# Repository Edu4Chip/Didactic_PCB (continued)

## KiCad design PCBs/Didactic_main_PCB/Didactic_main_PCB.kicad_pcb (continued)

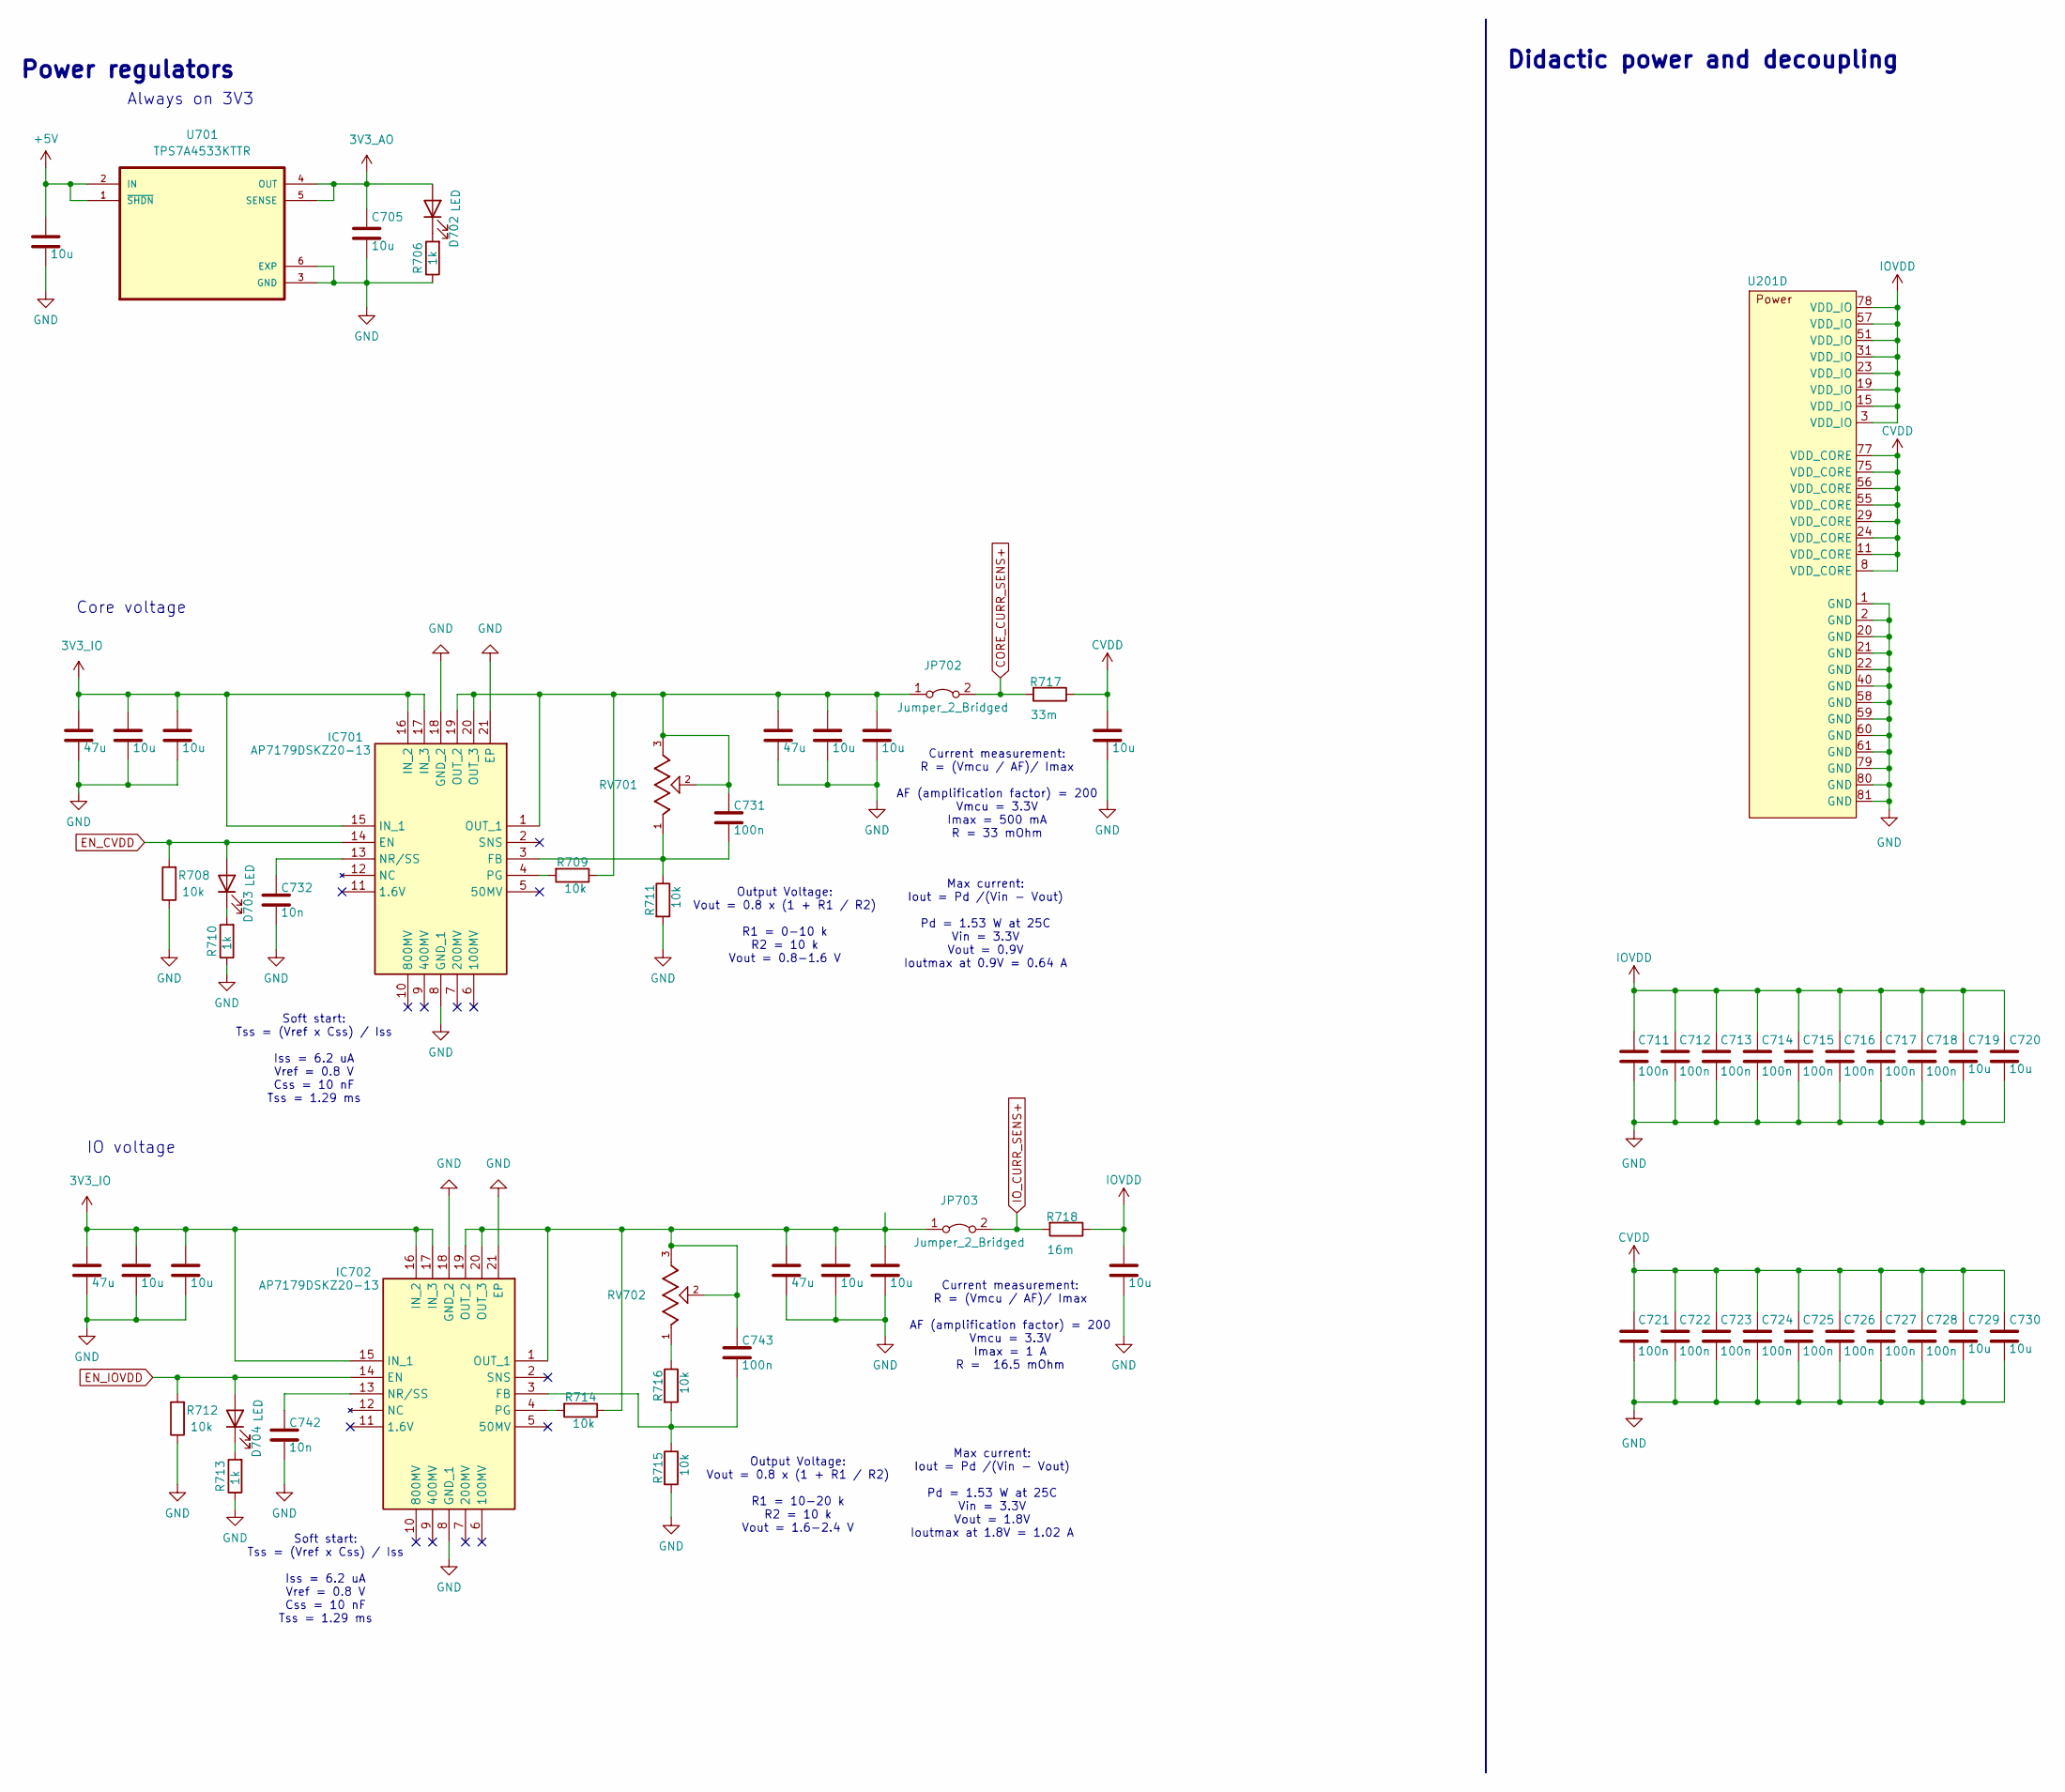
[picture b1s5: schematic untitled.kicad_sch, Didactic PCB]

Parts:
C703, C705, C719, C720, C729, C730, C734, C735, C737, C738, C740, C741, C745, C746, C747, C748: 10u; C_0805_2012Metric; MANUFACTURER_PART_NUMBER GPC0805106-25
C711, C712, C713, C714, C715, C716, C717, C718, C721, C722, C723, C724, C725, C726, C727, C728, C731, C743: 100n; C_0603_1608Metric; MANUFACTURER_PART_NUMBER GPC0603104
C732, C742: 10n; C_0603_1608Metric; MANUFACTURER_PART_NUMBER GPC0603103
C733, C736, C739, C744: 47u; C_0805_2012Metric; MANUFACTURER_PART_NUMBER GPC0805476-6.3
D702, D703, D704: LED; LED_0603_1608Metric; MANUFACTURER_PART_NUMBER APHD1608LSURCK
IC701, IC702: AP7179DSKZ20-13; QFN50P350X350X80-21N-D; Manufacturer_Part_Number AP7179DSKZ20-13
JP702, JP703: Jumper_2_Bridged; PinHeader_1x02_P2.54mm_Vertical; MANUFACTURER_PART_NUMBER 61300211121
R706, R710, R713: 1k; R_0603_1608Metric; MANUFACTURER_PART_NUMBER GPR06031K
R708, R709, R711, R712, R714, R715, R716: 10k; R_0603_1608Metric; MANUFACTURER_PART_NUMBER GPR060310K
R717: 33m; R_1206_3216Metric; MANUFACTURER_PART_NUMBER ERJ-8CWFR033V
R718: 16m; R_1206_3216Metric; MANUFACTURER_PART_NUMBER ERJ-8CWFR016V
RV701, RV702: PV36W103C01B00; TRIM_PV36W103C01B00; PARTREV N/A
U201: Didactic_QFN-80_EP_12x12_Pitch0.5mm
U701: TPS7A4533KTTR; VREG_TPS79625KTTR; MANUFACTURER_PART_NUMBER TPS7A4533KTTR

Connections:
3V3_AO: C705.2, D702.2 (A), U701.4 (OUT), U701.5 (SENSE); also elsewhere on the board
3V3_IO: C736.2, C737.2, C738.2, C739.2, C740.2, C741.2, IC701.15 (IN_1), IC701.16 (IN_2), IC701.17 (IN_3), IC702.15 (IN_1), IC702.16 (IN_2), IC702.17 (IN_3); also elsewhere on the board
+5V: C703.2, U701.1 (~SHDN), U701.2 (IN); also elsewhere on the board
CORE_CURR_SENS+: JP702.2 (B), R717.2; also elsewhere on the board
CVDD: C721.2, C722.2, C723.2, C724.2, C725.2, C726.2, C727.2, C728.2, C729.2, C730.2, C747.2, R717.1, U201.8 (VDD_CORE), U201.11 (VDD_CORE), U201.24 (VDD_CORE), U201.29 (VDD_CORE), U201.55 (VDD_CORE), U201.56 (VDD_CORE), U201.75 (VDD_CORE), U201.77 (VDD_CORE); also elsewhere on the board
EN_CVDD: D703.2 (A), IC701.14 (EN), R708.2; also elsewhere on the board
EN_IOVDD: D704.2 (A), IC702.14 (EN), R712.2; also elsewhere on the board
GND: C703.1, C705.1, C711.1, C712.1, C713.1, C714.1, C715.1, C716.1, C717.1, C718.1, C719.1, C720.1, C721.1, C722.1, C723.1, C724.1, C725.1, C726.1, C727.1, C728.1, C729.1, C730.1, C732.2, C733.1, C734.1, C735.1, C736.1, C737.1, C738.1, C739.1, C740.1, C741.1, C742.2, C744.1, C745.1, C746.1, C747.1, C748.1, IC701.8 (GND_1), IC701.18 (GND_2), IC701.21 (EP), IC702.8 (GND_1), IC702.18 (GND_2), IC702.21 (EP), R706.1, R708.1, R710.1, R711.2, R712.1, R713.1, R715.2, U201.1 (GND), U201.2 (GND), U201.20 (GND), U201.21 (GND), U201.22 (GND), U201.40 (GND), U201.58 (GND), U201.59 (GND), U201.60 (GND), U201.61 (GND), U201.79 (GND), U201.80 (GND), U201.81 (GND), U701.3 (GND), U701.6 (EXP); also elsewhere on the board
IOVDD: C711.2, C712.2, C713.2, C714.2, C715.2, C716.2, C717.2, C718.2, C719.2, C720.2, C748.2, R718.1, U201.3 (VDD_IO), U201.15 (VDD_IO), U201.19 (VDD_IO), U201.23 (VDD_IO), U201.31 (VDD_IO), U201.51 (VDD_IO), U201.57 (VDD_IO), U201.78 (VDD_IO); also elsewhere on the board
IO_CURR_SENS+: JP703.2 (B), R718.2; also elsewhere on the board
unnamed: D702.1 (K), R706.2
unnamed: D703.1 (K), R710.2
unnamed: D704.1 (K), R713.2
unnamed: C731.2, IC701.3 (FB), R711.1, RV701.1
unnamed: C732.1, IC701.13 (NR/SS)
unnamed: C731.1, C733.2, C734.2, C735.2, IC701.1 (OUT_1), IC701.19 (OUT_2), IC701.20 (OUT_3), JP702.1 (A), R709.1, RV701.2, RV701.3
unnamed: IC701.4 (PG), R709.2
unnamed: C743.2, IC702.3 (FB), R715.1, R716.2
unnamed: C742.1, IC702.13 (NR/SS)
unnamed: C743.1, C744.2, C745.2, C746.2, IC702.1 (OUT_1), IC702.19 (OUT_2), IC702.20 (OUT_3), JP703.1 (A), R714.1, RV702.2, RV702.3
unnamed: IC702.4 (PG), R714.2
unnamed: R716.1, RV702.1

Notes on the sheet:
Current measurement: R = (Vmcu / AF)/ Imax AF (amplification factor) = 200 Vmcu = 3.3V Imax = 1 A R = 16.5 mOhm
IO voltage
Soft start: Tss = (Vref x Css) / Iss Iss = 6.2 uA Vref = 0.8 V Css = 10 nF Tss = 1.29 ms
Max current: Iout = Pd /(Vin - Vout) Pd = 1.53 W at 25C Vin = 3.3V Vout = 0.9V Ioutmax at 0.9V = 0.64 A
Output Voltage: Vout = 0.8 x (1 + R1 / R2) R1 = 10-20 k R2 = 10 k Vout = 1.6-2.4 V
Always on 3V3
Core voltage
Power regulators
Didactic power and decoupling
Max current: Iout = Pd /(Vin - Vout) Pd = 1.53 W at 25C Vin = 3.3V Vout = 1.8V Ioutmax at 1.8V = 1.02 A
Current measurement: R = (Vmcu / AF)/ Imax AF (amplification factor) = 200 Vmcu = 3.3V Imax = 500 mA R = 33 mOhm
Output Voltage: Vout = 0.8 x (1 + R1 / R2) R1 = 0-10 k R2 = 10 k Vout = 0.8-1.6 V

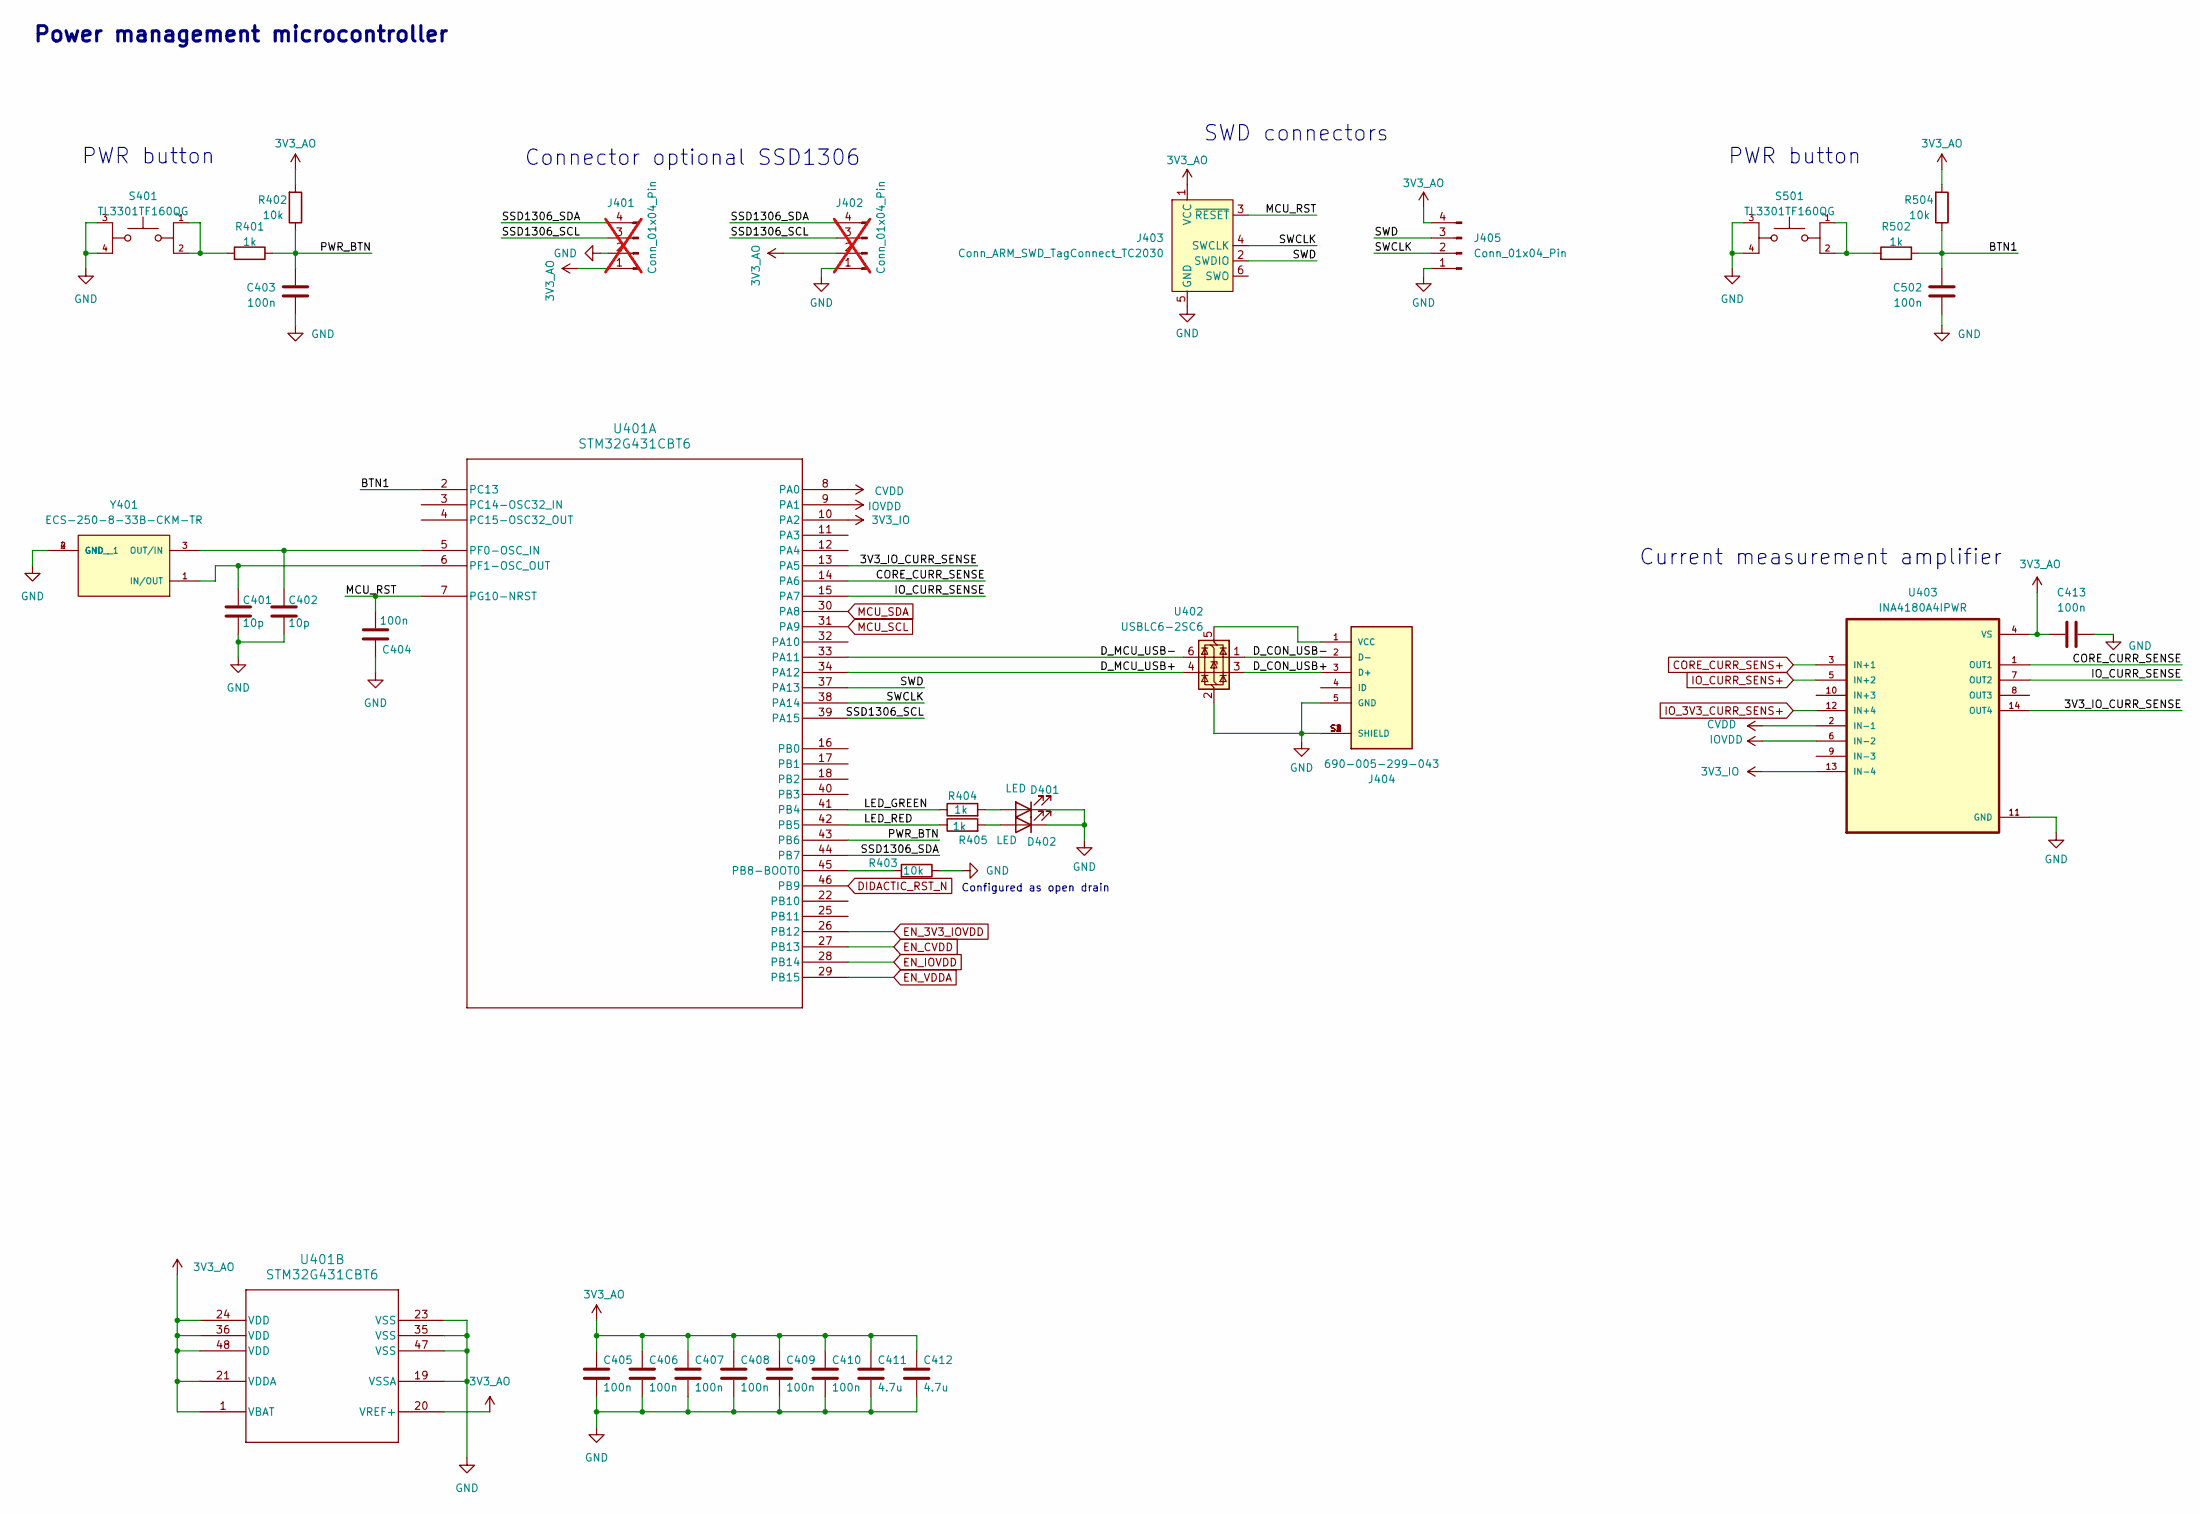
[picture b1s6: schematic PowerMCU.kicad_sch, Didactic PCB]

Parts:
C401, C402: 10p; C_0603_1608Metric; MANUFACTURER_PART_NUMBER GPC0603100
C403, C404, C405, C406, C407, C408, C409, C410, C413, C502: 100n; C_0603_1608Metric; MANUFACTURER_PART_NUMBER GPC0603104
C411, C412: 4.7u; C_0603_1608Metric; MANUFACTURER_PART_NUMBER GPC0603475-10
D401: LED; LED_0603_1608Metric; MANUFACTURER_PART_NUMBER APHD1608LCGCK
D402: LED; LED_0603_1608Metric; MANUFACTURER_PART_NUMBER APHD1608LSURCK
J401, J402: Conn_01x04_Pin; PinHeader_1x04_P2.54mm_Vertical; MANUFACTURER_PART_NUMBER 77311-424-04LF; not fitted
J403: Conn_ARM_SWD_TagConnect_TC2030; Tag-Connect_TC2030-IDC-FP_2x03_P1.27mm_Vertical
J404: 690-005-299-043; EDAC_690-005-299-043; PARTREV 11
J405: Conn_01x04_Pin; PinHeader_1x04_P2.54mm_Vertical; MANUFACTURER_PART_NUMBER 77311-424-04LF
R401, R404, R405, R502: 1k; R_0603_1608Metric; MANUFACTURER_PART_NUMBER GPR06031K
R402, R403, R504: 10k; R_0603_1608Metric; MANUFACTURER_PART_NUMBER GPR060310K
S401, S501: TL3301TF160QG; SW_TL3301TF160QG; PARTREV E
U401: STM32G431CBT6; LQFP48-7x7mm; MANUFACTURER_PART_NUMBER STM32G431CBT6
U402: USBLC6-2SC6; SOT-23-6; MANUFACTURER_PART_NUMBER USBLC6-2SC6
U403: INA4180A4IPWR; SOP65P640X120-14N; MANUFACTURER_PART_NUMBER INA4180A4IPWR
Y401: ECS-250-8-33B-CKM-TR; XTAL_ECS-250-8-33B-CKM-TR; MANUFACTURER_PART_NUMBER ECS-250-8-33B-CKM-TR

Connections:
3V3_AO: C405.2, C406.2, C407.2, C408.2, C409.2, C410.2, C411.2, C412.2, C413.1, J401.1, J402.2, J403.1 (VCC), J405.4, R402.2, R504.2, U401.1 (VBAT), U401.20 (VREF+), U401.21 (VDDA), U401.24 (VDD), U401.36 (VDD), U401.48 (VDD), U403.4 (VS); also elsewhere on the board
3V3_IO: U401.10 (PA2), U403.13 (IN-4); also elsewhere on the board
/PowerMCU/3V3_IO_CURR_SENSE: U401.13 (PA5), U403.14 (OUT4)
/PowerMCU/BTN1: C502.1, R502.1, R504.1, U401.2 (PC13)
/PowerMCU/CORE_CURR_SENSE: U401.14 (PA6), U403.1 (OUT1)
/PowerMCU/D_CON_USB+: J404.3 (D+), U402.3 (I/O2)
/PowerMCU/D_CON_USB-: J404.2 (D-), U402.1 (I/O1)
/PowerMCU/D_MCU_USB+: U401.34 (PA12), U402.4 (I/O2)
/PowerMCU/D_MCU_USB-: U401.33 (PA11), U402.6 (I/O1)
/PowerMCU/IO_CURR_SENSE: U401.15 (PA7), U403.7 (OUT2)
/PowerMCU/LED_GREEN: R404.1, U401.41 (PB4)
/PowerMCU/LED_RED: R405.1, U401.42 (PB5)
/PowerMCU/MCU_RST: C404.2, J403.3 (~RESET), U401.7 (PG10-NRST)
/PowerMCU/PWR_BTN: C403.1, R401.1, R402.1, U401.43 (PB6)
/PowerMCU/SSD1306_SCL: J401.3, J402.3, U401.39 (PA15)
/PowerMCU/SSD1306_SDA: J401.4, J402.4, U401.44 (PB7)
/PowerMCU/SWCLK: J403.4 (SWCLK), J405.2, U401.38 (PA14)
/PowerMCU/SWD: J403.2 (SWDIO), J405.3, U401.37 (PA13)
CORE_CURR_SENS+: U403.3 (IN+1); also elsewhere on the board
CVDD: U401.8 (PA0), U403.2 (IN-1); also elsewhere on the board
DIDACTIC_RST_N: U401.46 (PB9); also elsewhere on the board
EN_3V3_IOVDD: U401.26 (PB12); also elsewhere on the board
EN_CVDD: U401.27 (PB13); also elsewhere on the board
EN_IOVDD: U401.28 (PB14); also elsewhere on the board
EN_VDDA: U401.29 (PB15)
GND: C401.2, C402.2, C403.2, C404.1, C405.1, C406.1, C407.1, C408.1, C409.1, C410.1, C411.1, C412.1, C413.2, C502.2, D401.1 (K), D402.1 (K), J401.2, J402.1, J403.5 (GND), J404.5 (GND), J404.S1 (SHIELD), J404.S2 (SHIELD), J404.S3 (SHIELD), J404.S4 (SHIELD), J405.1, R403.1, S401.3, S401.4, S501.3, S501.4, U401.19 (VSSA), U401.23 (VSS), U401.35 (VSS), U401.47 (VSS), U402.2 (GND), U403.11 (GND), Y401.2 (GND), Y401.4 (GND__1); also elsewhere on the board
IOVDD: U401.9 (PA1), U403.6 (IN-2); also elsewhere on the board
IO_3V3_CURR_SENS+: U403.12 (IN+4); also elsewhere on the board
IO_CURR_SENS+: U403.5 (IN+2); also elsewhere on the board
MCU_SCL: U401.31 (PA9); also elsewhere on the board
MCU_SDA: U401.30 (PA8); also elsewhere on the board
unnamed: D401.2 (A), R404.2
unnamed: D402.2 (A), R405.2
unnamed: J404.1 (VCC), U402.5 (VBUS)
unnamed: R401.2, S401.1, S401.2
unnamed: R502.2, S501.1, S501.2
unnamed: R403.2, U401.45 (PB8-BOOT0)
unnamed: C402.1, U401.5 (PF0-OSC_IN), Y401.3 (OUT/IN)
unnamed: C401.1, U401.6 (PF1-OSC_OUT), Y401.1 (IN/OUT)

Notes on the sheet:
PWR button
Power management microcontroller
Connector optional SSD1306
Configured as open drain
SWD connectors
Current measurement amplifier

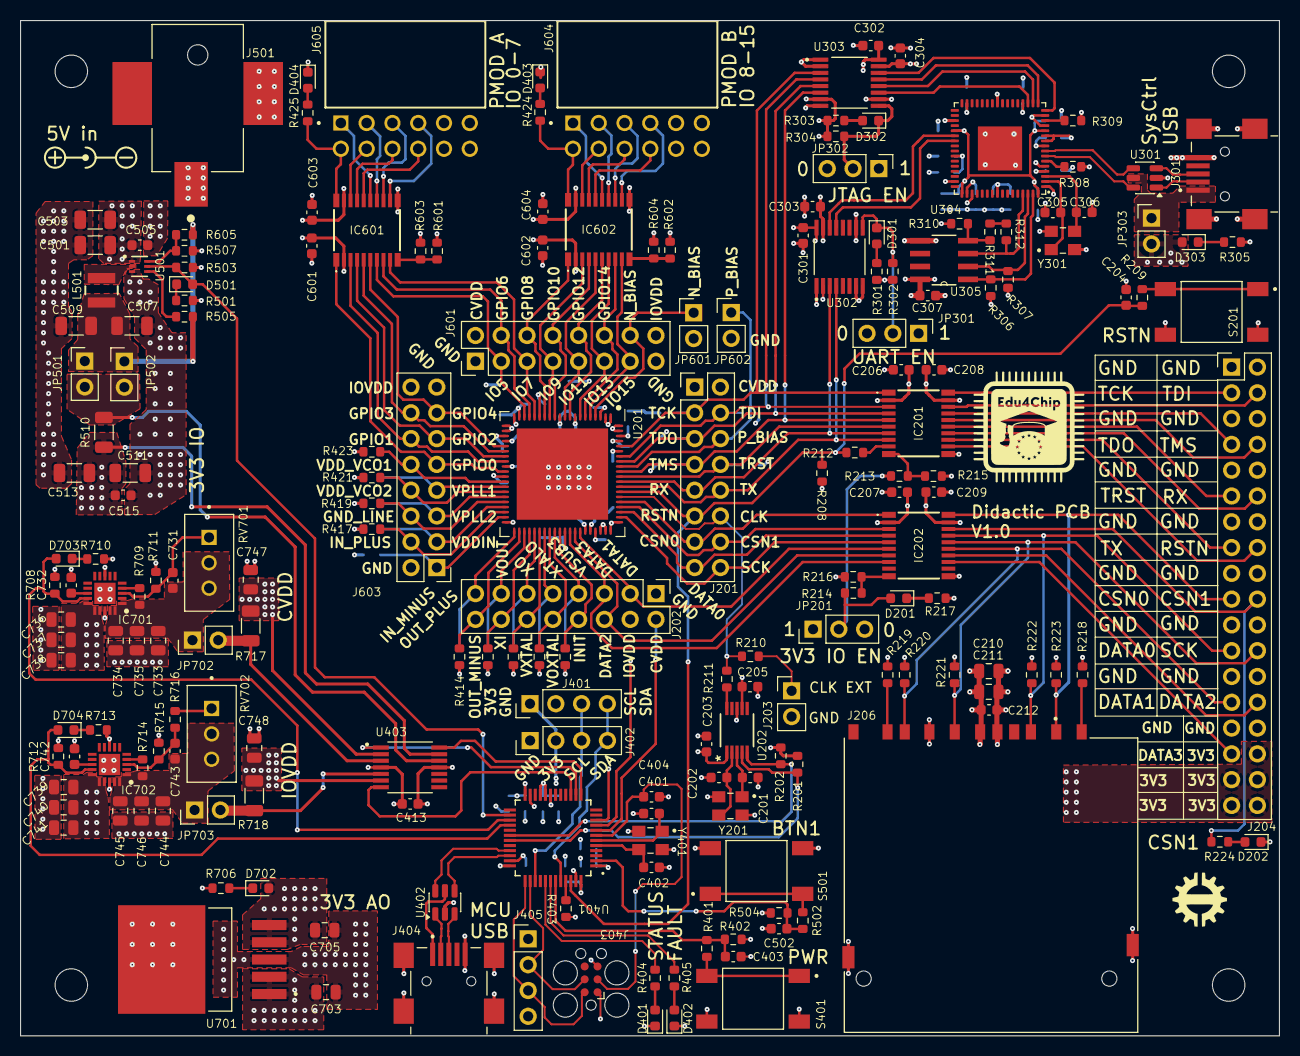
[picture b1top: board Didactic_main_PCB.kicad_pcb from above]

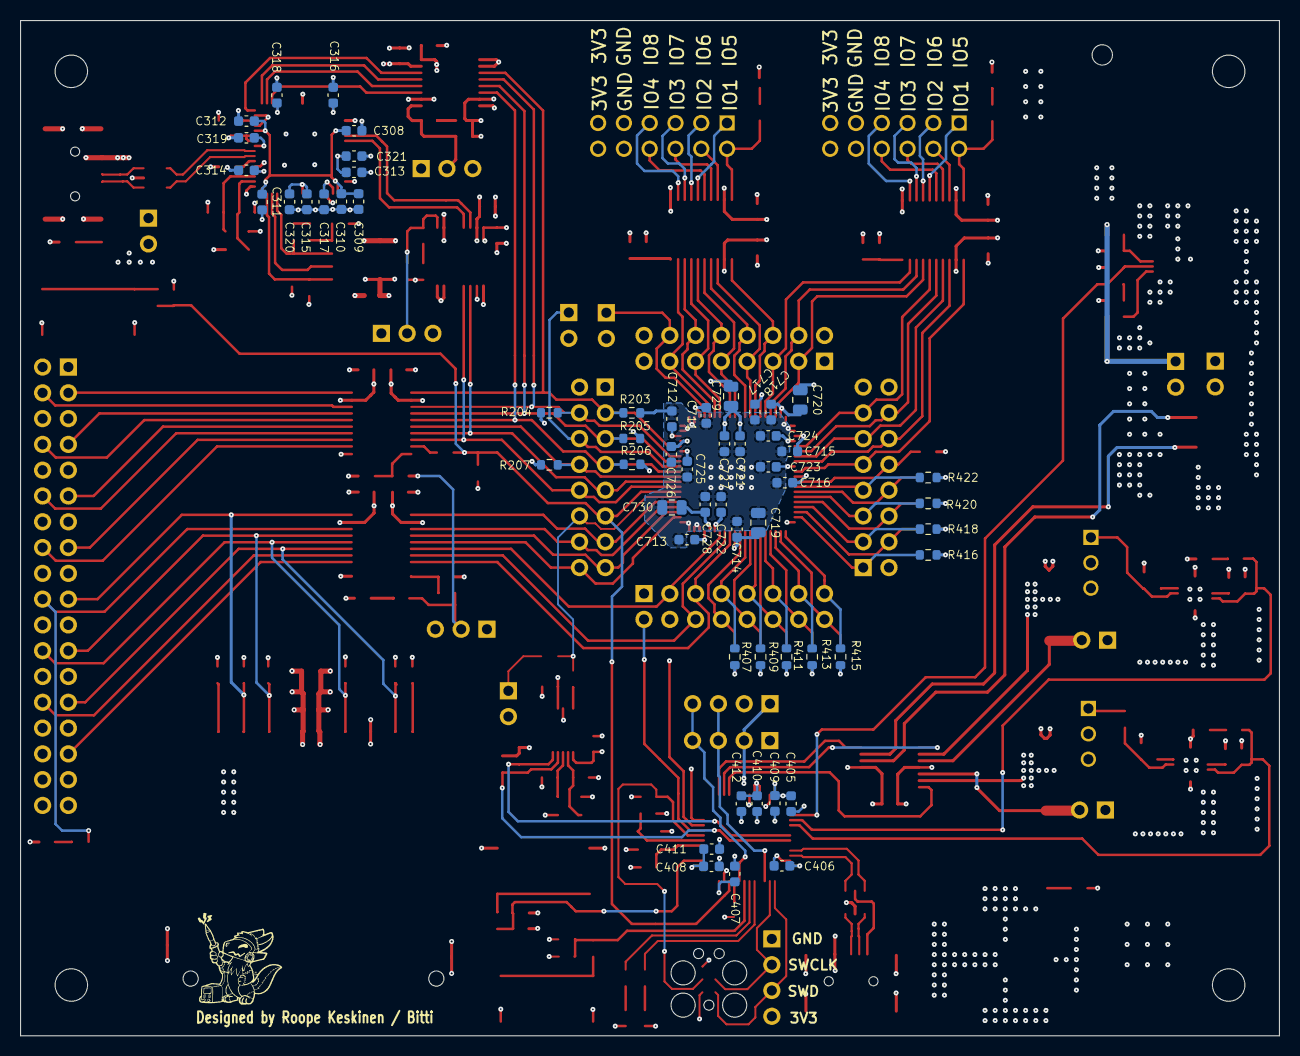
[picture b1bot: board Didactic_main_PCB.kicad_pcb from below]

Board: 4 copper layers, 124.0 x 100.0 mm, 250 parts (56 on the bottom side), 181 nets.

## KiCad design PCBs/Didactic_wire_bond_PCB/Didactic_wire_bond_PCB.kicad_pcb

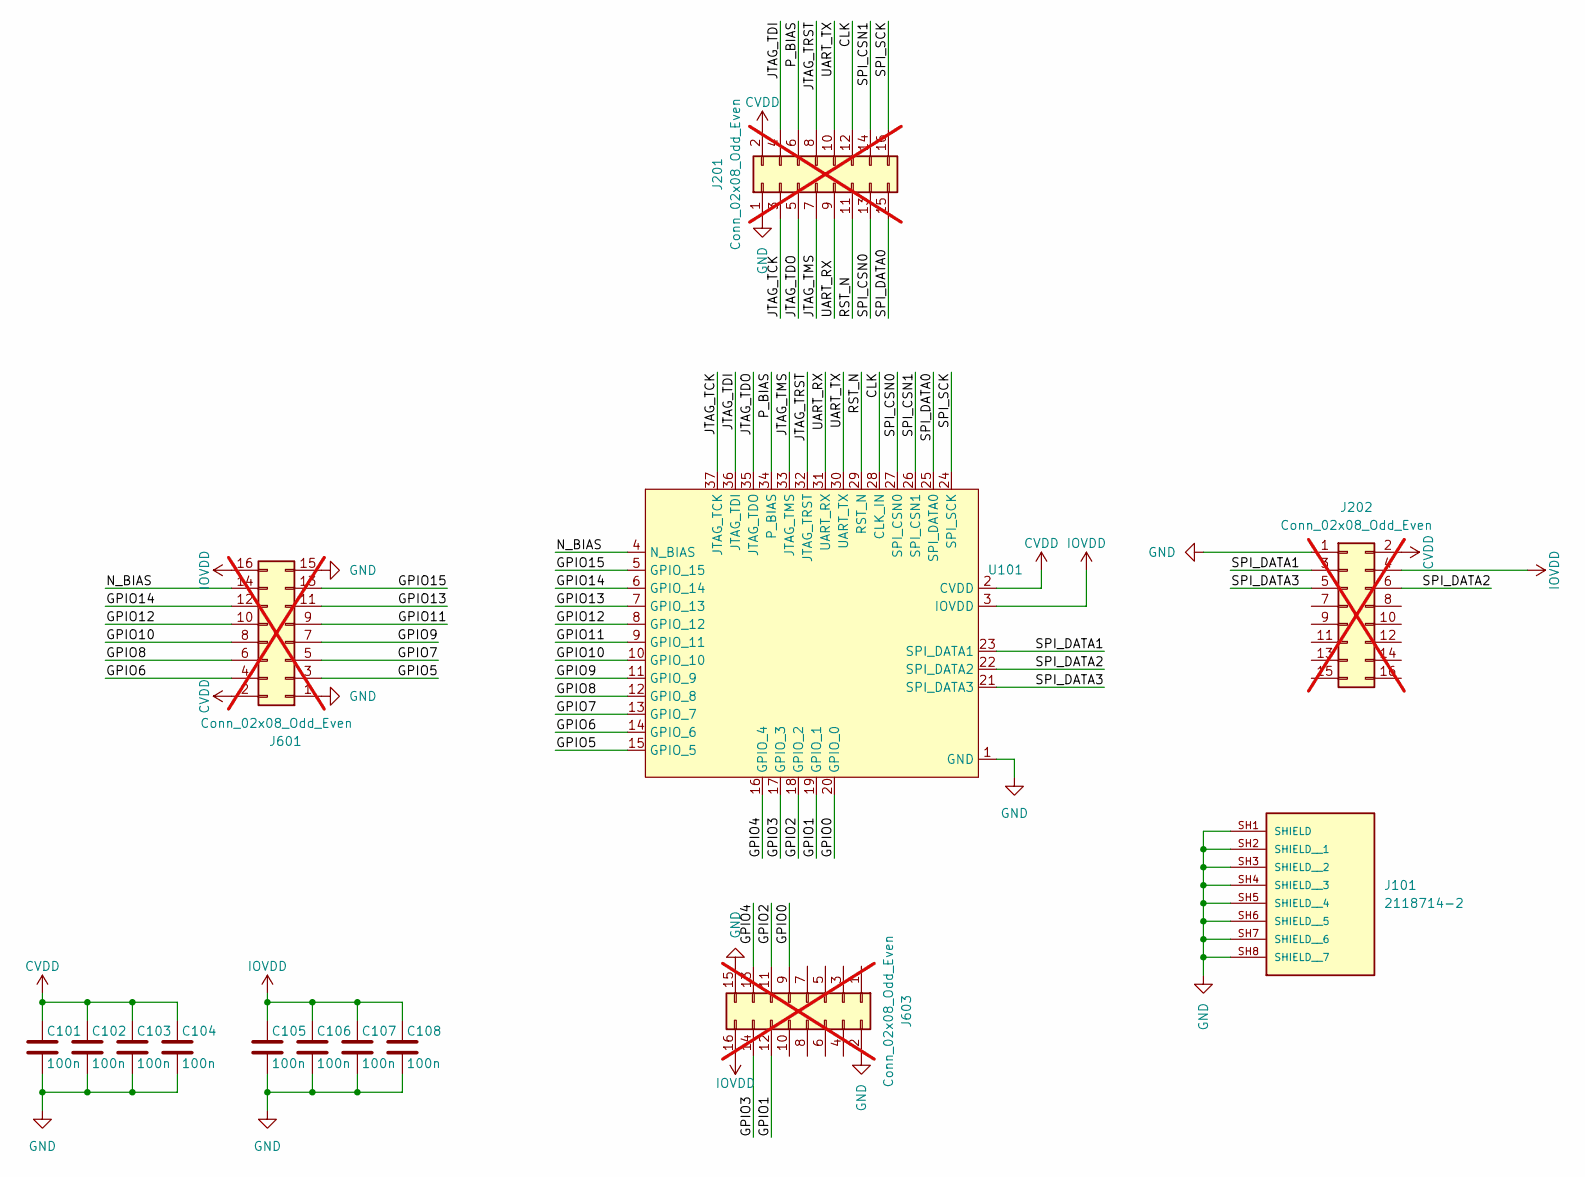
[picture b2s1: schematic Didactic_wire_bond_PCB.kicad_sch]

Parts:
C101, C102, C103, C104, C105, C106, C107, C108: 100n; C_0402_1005Metric
J101: 2118714-2; TE_2118714-2; PARTREV A2
J201, J202, J601, J603: Conn_02x08_Odd_Even; PinHeader_2x08_P2.54mm_Vertical; not fitted
U101: Didactic_WB

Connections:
/CLK: J201.12, U101.28 (CLK_IN)
/GPIO0: J603.9, U101.20 (GPIO_0)
/GPIO1: J603.12, U101.19 (GPIO_1)
/GPIO2: J603.11, U101.18 (GPIO_2)
/GPIO3: J603.14, U101.17 (GPIO_3)
/GPIO4: J603.13, U101.16 (GPIO_4)
/GPIO5: J601.3, U101.15 (GPIO_5)
/GPIO6: J601.4, U101.14 (GPIO_6)
/GPIO7: J601.5, U101.13 (GPIO_7)
/GPIO8: J601.6, U101.12 (GPIO_8)
/GPIO9: J601.7, U101.11 (GPIO_9)
/GPIO10: J601.8, U101.10 (GPIO_10)
/GPIO11: J601.9, U101.9 (GPIO_11)
/GPIO12: J601.10, U101.8 (GPIO_12)
/GPIO13: J601.11, U101.7 (GPIO_13)
/GPIO14: J601.12, U101.6 (GPIO_14)
/GPIO15: J601.13, U101.5 (GPIO_15)
/JTAG_TCK: J201.3, U101.37 (JTAG_TCK)
/JTAG_TDI: J201.4, U101.36 (JTAG_TDI)
/JTAG_TDO: J201.5, U101.35 (JTAG_TDO)
/JTAG_TMS: J201.7, U101.33 (JTAG_TMS)
/JTAG_TRST: J201.8, U101.32 (JTAG_TRST)
/N_BIAS: J601.14, U101.4 (N_BIAS)
/P_BIAS: J201.6, U101.34 (P_BIAS)
/RST_N: J201.11, U101.29 (RST_N)
/SPI_CSN0: J201.13, U101.27 (SPI_CSN0)
/SPI_CSN1: J201.14, U101.26 (SPI_CSN1)
/SPI_DATA0: J201.15, U101.25 (SPI_DATA0)
/SPI_DATA1: J202.3, U101.23 (SPI_DATA1)
/SPI_DATA2: J202.6, U101.22 (SPI_DATA2)
/SPI_DATA3: J202.5, U101.21 (SPI_DATA3)
/SPI_SCK: J201.16, U101.24 (SPI_SCK)
/UART_RX: J201.9, U101.31 (UART_RX)
/UART_TX: J201.10, U101.30 (UART_TX)
CVDD: C101.1, C102.1, C103.1, C104.1, J201.2, J202.2, J601.2, U101.2 (CVDD)
GND: C101.2, C102.2, C103.2, C104.2, C105.2, C106.2, C107.2, C108.2, J101.SH1 (SHIELD), J101.SH2 (SHIELD__1), J101.SH3 (SHIELD__2), J101.SH4 (SHIELD__3), J101.SH5 (SHIELD__4), J101.SH6 (SHIELD__5), J101.SH7 (SHIELD__6), J101.SH8 (SHIELD__7), J201.1, J202.1, J601.1, J601.15, J603.2, J603.15, U101.1 (GND)
IOVDD: C105.1, C106.1, C107.1, C108.1, J202.4, J601.16, J603.16, U101.3 (IOVDD)

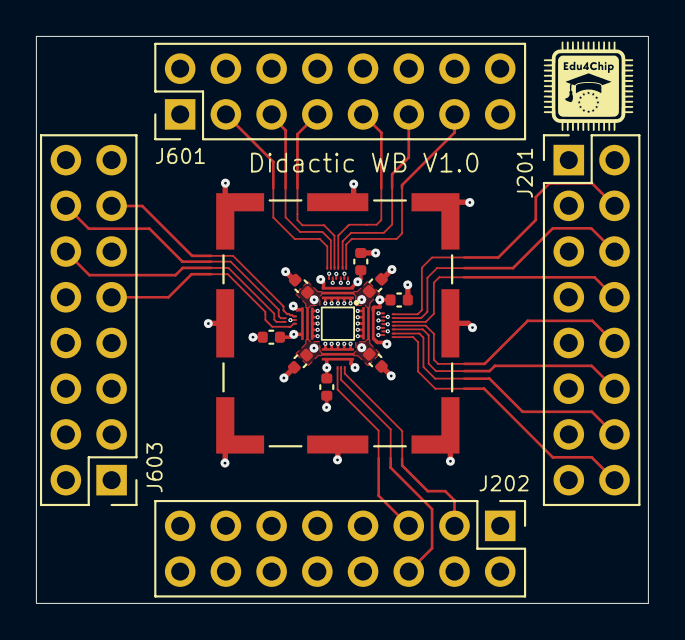
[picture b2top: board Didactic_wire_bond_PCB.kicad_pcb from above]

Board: 6 copper layers, 34.0 x 31.5 mm, 14 parts (0 on the bottom side), 37 nets.

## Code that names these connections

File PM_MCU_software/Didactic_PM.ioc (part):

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Mcu.Name=STM32G431C(6-8-B)Tx
Mcu.Package=LQFP48
Mcu.UserName=STM32G431CBTx
PA0.GPIOParameters=GPIO_Label
PA0.GPIO_Label=CVDD_VOLTAGE
PA0.Mode=IN1-Single-Ended
PA0.Signal=ADC1_IN1
PA1.GPIOParameters=GPIO_Label
PA1.GPIO_Label=IOVDD_VOLTAGE
PA1.Mode=IN2-Single-Ended
PA1.Signal=ADC1_IN2
PA11.Mode=Device
PA11.Signal=USB_DM
PA12.Mode=Device
PA12.Signal=USB_DP
PA13.Mode=Trace_Asynchronous_SW
PA13.Signal=SYS_JTMS-SWDIO
PA14.Mode=Trace_Asynchronous_SW
PA14.Signal=SYS_JTCK-SWCLK
PA15.Mode=I2C
PA15.Signal=I2C1_SCL
PA2.GPIOParameters=GPIO_Label
PA2.GPIO_Label=IOVDD3V3_VOLTAGE
PA2.Mode=IN3-Single-Ended
PA2.Signal=ADC1_IN3
PA5.GPIOParameters=GPIO_Label
PA5.GPIO_Label=IOVDD3V3_CURRENT
PA5.Mode=IN13-Single-Ended
PA5.Signal=ADC2_IN13
PA6.GPIOParameters=GPIO_Label
PA6.GPIO_Label=CVDD_CURRENT
PA6.Mode=IN3-Single-Ended
PA6.Signal=ADC2_IN3
PA7.GPIOParameters=GPIO_Label
PA7.GPIO_Label=IOVDD_CURRENT
PA7.Mode=IN4-Single-Ended
PA7.Signal=ADC2_IN4
PA8.Mode=I2C
PA8.Signal=I2C2_SDA
PA9.Mode=I2C
PA9.Signal=I2C2_SCL
PB12.GPIOParameters=GPIO_Label
PB12.GPIO_Label=EN_IOVDD3V3
PB12.Signal=GPIO_Output
PB13.GPIOParameters=GPIO_Label
PB13.GPIO_Label=EN_CVDD
PB13.Signal=GPIO_Output
PB14.GPIOParameters=GPIO_Label
PB14.GPIO_Label=EN_IOVDD
PB14.Signal=GPIO_Output
PB3.Mode=Trace_Asynchronous_SW
PB3.Signal=SYS_JTDO-SWO
PB4.GPIOParameters=GPIO_Label
PB4.GPIO_Label=LED_GREEN
PB4.Signal=GPIO_Output
PB5.GPIOParameters=GPIO_Label
PB5.GPIO_Label=LED_RED
PB5.Signal=GPIO_Output
PB6.GPIOParameters=GPIO_Label,GPIO_ModeDefaultEXTI
PB6.GPIO_Label=PWR_BTN
PB6.GPIO_ModeDefaultEXTI=GPIO_MODE_IT_FALLING
PB6.Signal=GPXTI6
PB7.Mode=I2C
PB7.Signal=I2C1_SDA
PB9.GPIOParameters=GPIO_PuPd,GPIO_Label,GPIO_ModeDefaultOutputPP
PB9.GPIO_Label=DIDACTIC_RSTN
PB9.GPIO_ModeDefaultOutputPP=GPIO_MODE_OUTPUT_OD
PB9.GPIO_PuPd=GPIO_NOPULL
PB9.Signal=GPIO_Output
PC13.GPIOParameters=GPIO_Label
PC13.GPIO_Label=USER_BTN
PC13.Signal=GPXTI13
PF0-OSC_IN.Mode=HSE-External-Oscillator
PF0-OSC_IN.Signal=RCC_OSC_IN
PF1-OSC_OUT.Mode=HSE-External-Oscillator
PF1-OSC_OUT.Signal=RCC_OSC_OUT
RCC.HSE_VALUE=25000000
RCC.SYSCLKFreq_VALUE=150000000
RCC.SYSCLKSource=RCC_SYSCLKSOURCE_PLLCLK
board=custom

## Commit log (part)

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2026-05-26 Created base structure for the repo and added documentation
2026-05-26 Added power management MCU software
2026-05-26 Added Didactic main PCB kicad project
2026-05-26 Added didactic wire bond PCB kicad project
2026-05-27 more updates to readme
